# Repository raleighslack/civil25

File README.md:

# civil25 - An 8088 SBC  
A 8088 based SBC. 512k of RAM. 256k of ROM.

This is a simple 8088 based SBC that doesnt aim for any kind of PC compatibility. This is just generally a project to learn about the 8088 and other processors.

Current assembler in use is NASM. I am working on the **Currently in progress** goals listed below, as well as software to support it along the way.

## Current Parts List

- 1x 80c88 CPU
- 2x 74HCT373 D-type Octal Latch
- 1x 74HCT245 Bus Trancever
- 2x 74HCT138 3-to-8 Decoder
- 1x SST39SF020A Flash
- 1x AS6C4008 RAM
- 1x 82c55A PPI
- 1x 82c59 PIC
- 1x 555/8284 Clock Generator(And supporting circuitry)
- 1x YM3812 FM Sound
- 1x TL072 Op-Amp
- 1x Y3014B DAC
- 1x LCD
- 100000x Jumper Wires

# Completed

- Base Computer
- 82c55 I/O plus LCD
- YM3812
- Schematics

# Currently in progress

- 82c59 Programmable Interrupt Controller
- PS/2 Keyboard
- Video Card using SCN2674B
- Add SD Card
- Real Time Clock + Battery

# Future additions (Hardware)

- PCB - Mini ITX - Compatible with ATX PSU's
- Ethernet - Currently looking at the `W5100S-L`
- DMA Controller (82c57)
- Timer (82c53/82c54)
- CMOS RAM to maintain system settings

## Future Aditions (Software)

- C Compiler
- Make BIOS
- Make Kernel
- Make C Standard Library
- Make UNIX Operating System

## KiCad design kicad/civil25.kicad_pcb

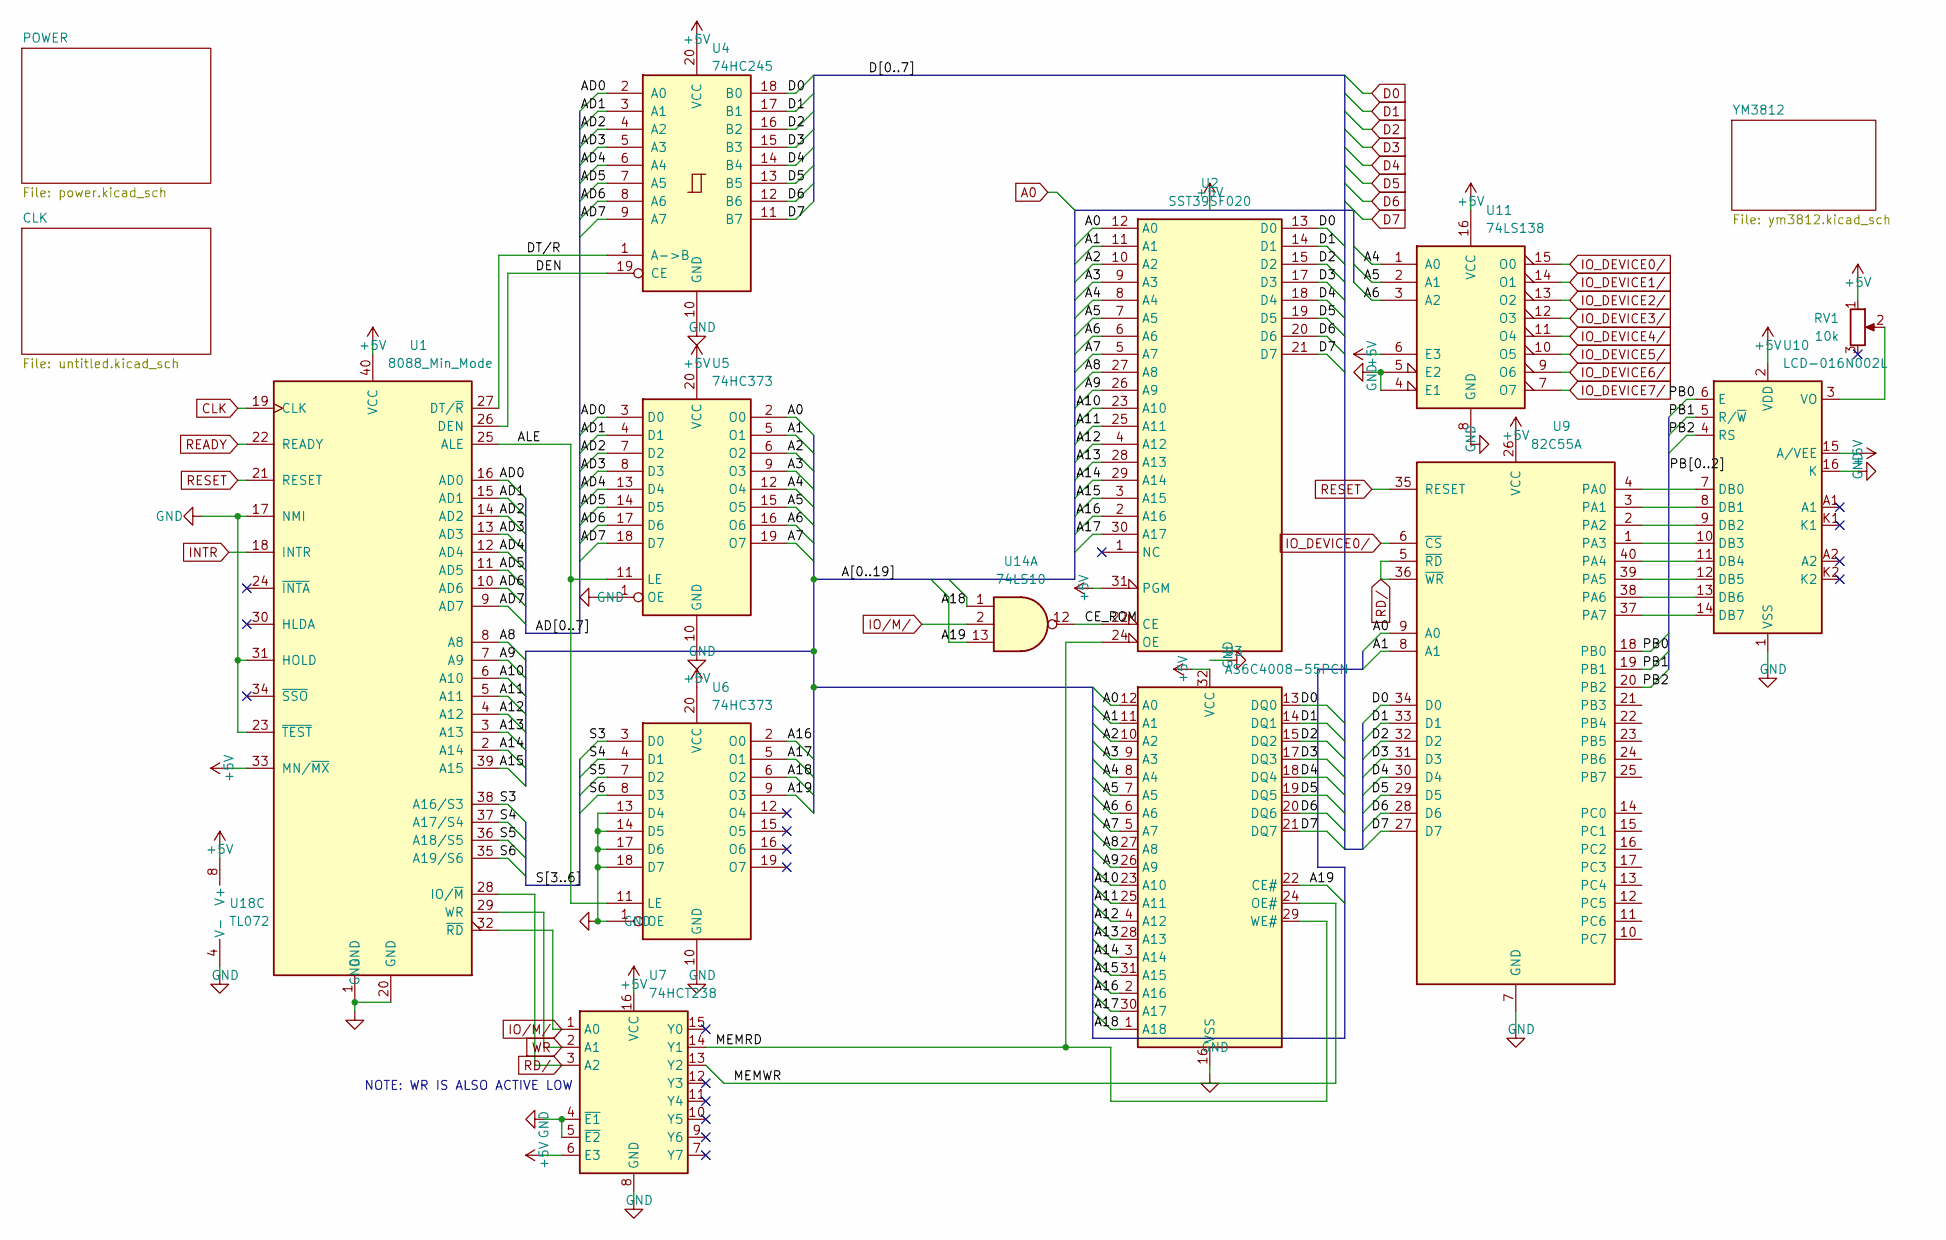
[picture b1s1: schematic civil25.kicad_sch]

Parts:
RV1: 10k; Potentiometer_ACP_CA9-V10_Vertical
U1: 8088_Min_Mode; DIP-40_W15.24mm
U2: SST39SF020; DIP_Socket-32_W11.9_W12.7_W15.24_W17.78_W18.5_3M_232-1285-0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
U3: AS6C4008-55PCN; DIP-32_W15.24mm
U4: 74HC245; DIP-20_W7.62mm_Socket
U5, U6: 74HC373; DIP-20_W7.62mm_Socket
U7: 74HCT238; DIP-16_W7.62mm_Socket
U9: 82C55A; DIP-40_W15.24mm
U10: LCD-016N002L; WC1602A
U11: 74LS138; DIP-16_W7.62mm_Socket
U14: 74LS10; DIP-14_W7.62mm_Socket
U18: TL072; DIP-8_W7.62mm_Socket

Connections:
+5V: RV1.1, U1.33 (MN/~MX), U1.40 (VCC), U2.31 (PGM), U2.32 (VCC), U3.32 (VCC), U4.20 (VCC), U5.20 (VCC), U6.20 (VCC), U7.6 (E3), U7.16 (VCC), U9.26 (VCC), U10.2 (VDD), U10.15 (A/VEE), U11.6 (E3), U11.16 (VCC), U18.8 (V+); also elsewhere on the board
/A1: U2.11 (A1), U3.11 (A1), U5.5 (O1), U9.8 (A1)
/A2: U2.10 (A2), U3.10 (A2), U5.6 (O2)
/A3: U2.9 (A3), U3.9 (A3), U5.9 (O3)
/A4: U2.8 (A4), U3.8 (A4), U5.12 (O4), U11.1 (A0)
/A5: U2.7 (A5), U3.7 (A5), U5.15 (O5), U11.2 (A1)
/A6: U2.6 (A6), U3.6 (A6), U5.16 (O6), U11.3 (A2)
/A7: U2.5 (A7), U3.5 (A7), U5.19 (O7)
/A8: U1.8 (A8), U2.27 (A8), U3.27 (A8)
/A9: U1.7 (A9), U2.26 (A9), U3.26 (A9)
/A10: U1.6 (A10), U2.23 (A10), U3.23 (A10)
/A11: U1.5 (A11), U2.25 (A11), U3.25 (A11)
/A12: U1.4 (A12), U2.4 (A12), U3.4 (A12)
/A13: U1.3 (A13), U2.28 (A13), U3.28 (A13)
/A14: U1.2 (A14), U2.29 (A14), U3.3 (A14)
/A15: U1.39 (A15), U2.3 (A15), U3.31 (A15)
/A16: U2.2 (A16), U3.2 (A16), U6.2 (O0)
/A17: U2.30 (A17), U3.30 (A17), U6.5 (O1)
/A18: U3.1 (A18), U6.6 (O2), U14.1
/A19: U3.22 (CE#), U6.9 (O3), U14.13
/AD0: U1.16 (AD0), U4.2 (A0), U5.3 (D0)
/AD1: U1.15 (AD1), U4.3 (A1), U5.4 (D1)
/AD2: U1.14 (AD2), U4.4 (A2), U5.7 (D2)
/AD3: U1.13 (AD3), U4.5 (A3), U5.8 (D3)
/AD4: U1.12 (AD4), U4.6 (A4), U5.13 (D4)
/AD5: U1.11 (AD5), U4.7 (A5), U5.14 (D5)
/AD6: U1.10 (AD6), U4.8 (A6), U5.17 (D6)
/AD7: U1.9 (AD7), U4.9 (A7), U5.18 (D7)
/ALE: U1.25 (ALE), U5.11 (LE), U6.11 (LE)
/CE_ROM: U2.22 (CE), U14.12
/DEN: U1.26 (DEN), U4.19 (CE)
/DT/R: U1.27 (DT/~R), U4.1 (A->B)
/MEMRD: U2.24 (OE), U3.29 (WE#), U7.14 (Y1)
/MEMWR: U3.24 (OE#), U7.13 (Y2)
/PB0: U9.18 (PB0), U10.6 (E)
/PB1: U9.19 (PB1), U10.5 (R/~W)
/PB2: U9.20 (PB2), U10.4 (RS)
/S3: U1.38 (A16/S3), U6.3 (D0)
/S4: U1.37 (A17/S4), U6.4 (D1)
/S5: U1.36 (A18/S5), U6.7 (D2)
/S6: U1.35 (A19/S6), U6.8 (D3)
A0: U2.12 (A0), U3.12 (A0), U5.2 (O0), U9.9 (A0); also elsewhere on the board
CLK: U1.19 (CLK); also elsewhere on the board
D0: U2.13 (D0), U3.13 (DQ0), U4.18 (B0), U9.34 (D0); also elsewhere on the board
D1: U2.14 (D1), U3.14 (DQ1), U4.17 (B1), U9.33 (D1); also elsewhere on the board
D2: U2.15 (D2), U3.15 (DQ2), U4.16 (B2), U9.32 (D2); also elsewhere on the board
D3: U2.17 (D3), U3.17 (DQ3), U4.15 (B3), U9.31 (D3); also elsewhere on the board
D4: U2.18 (D4), U3.18 (DQ4), U4.14 (B4), U9.30 (D4); also elsewhere on the board
D5: U2.19 (D5), U3.19 (DQ5), U4.13 (B5), U9.29 (D5); also elsewhere on the board
D6: U2.20 (D6), U3.20 (DQ6), U4.12 (B6), U9.28 (D6); also elsewhere on the board
D7: U2.21 (D7), U3.21 (DQ7), U4.11 (B7), U9.27 (D7); also elsewhere on the board
GND: U1.1 (GND), U1.17 (NMI), U1.20 (GND), U1.23 (~TEST), U1.31 (HOLD), U2.16 (GND), U3.16 (VSS), U4.10 (GND), U5.1 (OE), U5.10 (GND), U6.1 (OE), U6.10 (GND), U6.13 (D4), U6.14 (D5), U6.17 (D6), U6.18 (D7), U7.4 (~E1), U7.5 (~E2), U7.8 (GND), U9.7 (GND), U10.1 (VSS), U10.16 (K), U11.4 (E1), U11.5 (E2), U11.8 (GND), U18.4 (V-); also elsewhere on the board
INTR: U1.18 (INTR); also elsewhere on the board
IO_DEVICE0/: U9.6 (~CS), U11.15 (O0)
IO_DEVICE1/: U11.14 (O1); also elsewhere on the board
IO_DEVICE2/: U11.13 (O2)
IO_DEVICE3/: U11.12 (O3)
IO_DEVICE4/: U11.11 (O4)
IO_DEVICE5/: U11.10 (O5)
IO_DEVICE6/: U11.9 (O6)
IO_DEVICE7/: U11.7 (O7)
IO/M/: U1.32 (~RD), U7.1 (A0), U14.2
unnamed: RV1.2, U10.3 (VO)
unnamed: U9.4 (PA0), U10.7 (DB0)
unnamed: U9.3 (PA1), U10.8 (DB1)
unnamed: U9.2 (PA2), U10.9 (DB2)
unnamed: U9.1 (PA3), U10.10 (DB3)
unnamed: U9.40 (PA4), U10.11 (DB4)
unnamed: U9.39 (PA5), U10.12 (DB5)
unnamed: U9.38 (PA6), U10.13 (DB6)
unnamed: U9.37 (PA7), U10.14 (DB7)
RD/: U1.28 (IO/~M), U7.3 (A2), U9.5 (~RD), U9.36 (~WR); also elsewhere on the board
READY: U1.22 (READY); also elsewhere on the board
RESET: U1.21 (RESET), U9.35 (RESET); also elsewhere on the board
WR: U1.29 (WR), U7.2 (A1); also elsewhere on the board

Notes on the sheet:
NOTE: WR IS ALSO ACTIVE LOW

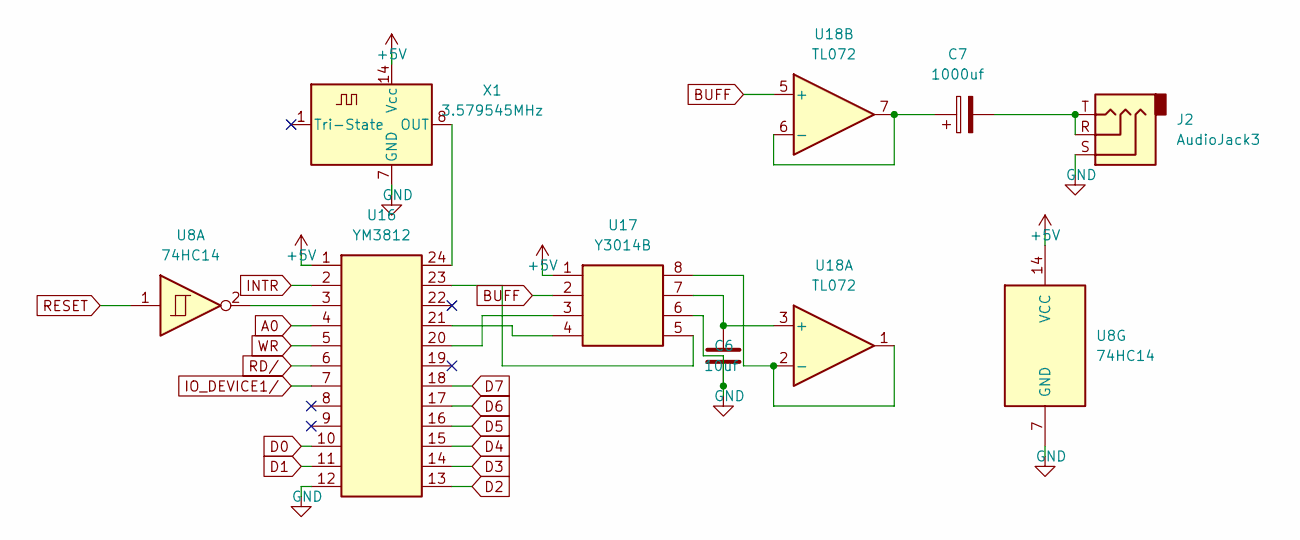
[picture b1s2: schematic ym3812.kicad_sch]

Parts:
C6: 10uf; CP_Radial_D5.0mm_P2.50mm
C7: 1000uf; CP_Radial_D5.0mm_P2.50mm
J2: AudioJack3; Jack_3.5mm_CUI_SJ1-3533NG_Horizontal_CircularHoles
U8: 74HC14; DIP-14_W7.62mm_Socket
U16: YM3812; DIP-24_W15.24mm_Socket
U17: Y3014B; DIP-8_W7.62mm_Socket
U18: TL072; DIP-8_W7.62mm_Socket
X1: 3.579545MHz; Oscillator_DIP-14

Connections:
+5V: U8.14 (VCC), U16.1, U17.1, X1.14 (Vcc); also elsewhere on the board
A0: U16.4; also elsewhere on the board
BUFF: U17.2, U18.5 (+)
D0: U16.10; also elsewhere on the board
D1: U16.11; also elsewhere on the board
D2: U16.13; also elsewhere on the board
D3: U16.14; also elsewhere on the board
D4: U16.15; also elsewhere on the board
D5: U16.16; also elsewhere on the board
D6: U16.17; also elsewhere on the board
D7: U16.18; also elsewhere on the board
GND: C6.2, J2.S, U8.7 (GND), U16.12, U17.6, X1.7 (GND); also elsewhere on the board
INTR: U16.2; also elsewhere on the board
IO_DEVICE1/: U16.7; also elsewhere on the board
unnamed: C6.1, U17.7, U18.3 (+)
unnamed: C7.1, U18.6 (-), U18.7
unnamed: C7.2, J2.R, J2.T
unnamed: U8.2, U16.3
unnamed: U16.20, U17.3
unnamed: U16.21, U17.4
unnamed: U16.23, U17.5
unnamed: U16.24, X1.8 (OUT)
unnamed: U17.8, U18.1, U18.2 (-)
RD/: U16.6; also elsewhere on the board
RESET: U8.1; also elsewhere on the board
WR: U16.5; also elsewhere on the board

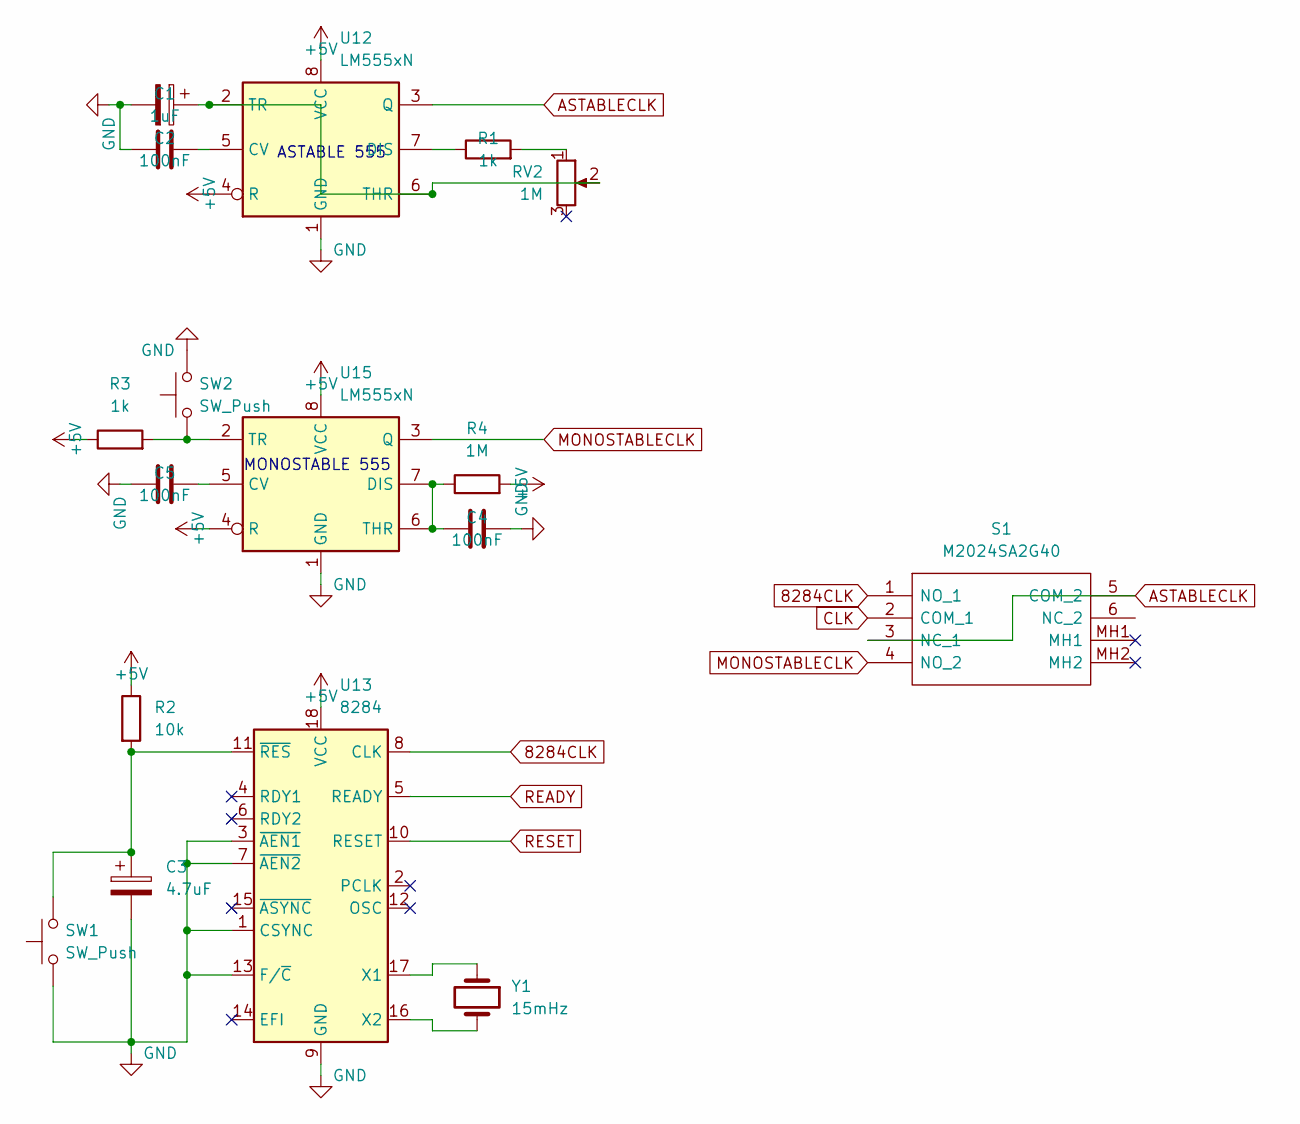
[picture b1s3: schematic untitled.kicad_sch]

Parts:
C1: 1uF; CP_Radial_D5.0mm_P2.50mm
C2, C4, C5: 100nF; C_Disc_D6.0mm_W2.5mm_P5.00mm
C3: 4.7uF; CP_Radial_D5.0mm_P2.50mm
R1, R3: 1k; R_Axial_DIN0204_L3.6mm_D1.6mm_P5.08mm_Horizontal
R2: 10k; R_Axial_DIN0204_L3.6mm_D1.6mm_P5.08mm_Horizontal
R4: 1M; R_Axial_DIN0204_L3.6mm_D1.6mm_P5.08mm_Horizontal
RV2: 1M; Potentiometer_ACP_CA9-V10_Vertical
S1: M2024SA2G40; Mouser Part Number 633-M2024SA2G40
SW1, SW2: SW_Push; SW_PUSH_6mm_H4.3mm
U12, U15: LM555xN; DIP-8_W7.62mm
U13: 8284; DIP-18_W7.62mm
Y1: 15mHz; Crystal_HC18-U_Vertical

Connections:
8284CLK: S1.1 (NO_1), U13.8 (CLK)
+5V: R2.1, R3.1, R4.2, U12.4 (R), U12.8 (VCC), U13.18 (VCC), U15.4 (R), U15.8 (VCC); also elsewhere on the board
ASTABLECLK: S1.3 (NC_1), S1.5 (COM_2), U12.3 (Q)
CLK: S1.2 (COM_1); also elsewhere on the board
GND: C1.2, C2.1, C3.2, C4.2, C5.1, SW1.1, SW2.2, U12.1 (GND), U13.1 (CSYNC), U13.3 (~AEN1), U13.7 (~AEN2), U13.9 (GND), U13.13 (F/~C), U15.1 (GND); also elsewhere on the board
MONOSTABLECLK: S1.4 (NO_2), U15.3 (Q)
unnamed: C1.1, RV2.2, U12.2 (TR), U12.6 (THR)
unnamed: C2.2, U12.5 (CV)
unnamed: C3.1, R2.2, SW1.2, U13.11 (~RES)
unnamed: C4.1, R4.1, U15.6 (THR), U15.7 (DIS)
unnamed: C5.2, U15.5 (CV)
unnamed: R1.1, U12.7 (DIS)
unnamed: R1.2, RV2.1
unnamed: R3.2, SW2.1, U15.2 (TR)
unnamed: U13.16 (X2), Y1.2
unnamed: U13.17 (X1), Y1.1
READY: U13.5 (READY); also elsewhere on the board
RESET: U13.10 (RESET); also elsewhere on the board

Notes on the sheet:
MONOSTABLE 555
ASTABLE 555

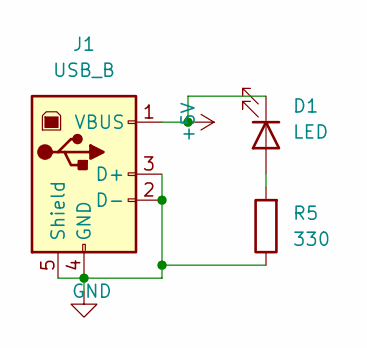
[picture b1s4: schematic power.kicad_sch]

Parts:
D1: LED; LED_D5.0mm
J1: USB_B; USB_B_Lumberg_2411_02_Horizontal
R5: 330; R_Axial_DIN0204_L3.6mm_D1.6mm_P5.08mm_Horizontal

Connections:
+5V: D1.1 (K), J1.1 (VBUS); also elsewhere on the board
GND: J1.2 (D-), J1.3 (D+), J1.4 (GND), J1.5 (Shield), R5.1; also elsewhere on the board
unnamed: D1.2 (A), R5.2

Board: 2 copper layers, 40 parts (0 on the bottom side), 93 nets, no tracks yet.

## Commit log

2022-08-20 add bcc
2022-08-20 first test on sbc
2022-08-27 add nasm
2022-08-29 add arduino monitors
2022-09-09 change README/update NASM
2022-09-11 update NASM
2022-09-17 I/O and RAM
2022-09-24 Efficient Hello World
2022-10-03 PCB/gcc
2022-10-04 working gcc
2022-10-12 remove unused assemblers/update gcc
2022-10-12 update PCB
2022-12-22 update gcc
2022-12-23 stable
    Current, stable code
2022-12-23 working gcc as linker
2022-12-23 g++ as linker
2022-12-30 Working print string
2022-12-31 New lcd functions
2022-12-31 Make lcd_init
2023-01-03 change dumpfile for nasm
2023-01-04 make ramtest()
2023-01-04 working memory test
2023-02-11 Working ivt
2023-02-11 keyboard
2023-02-11 Small changes
2023-03-14 reset vec workaround
2023-03-15 All in on C
2023-03-15 Update action/make hello world
2023-03-15 Reinstate keyboard code
